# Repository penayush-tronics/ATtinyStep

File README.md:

# ATtinyStep

ATtinyStep is a compact, rechargeable, and portable offline step counter as well as speedometer. It helps in reaching your step goals at a healthy pace, while enjoying the outside world instead of doomscrolling with your neck down. It uses a 6-axis Accelrometer+Gyro IMU (Interital Measurment Unit) and the processing capabilities of the ATtiny1624 to easily count your steps automatically. As a bonus, it doubles as breakout board for the ATtiny1624, so it can be used for more projects other than a speedometer.

## How to use the ATtinyStep
Here is a labelled diagram:

#### As step counter
Connect a single cell 3.7V li-ion battery to the battery header (with correct polarity; labelled on the back). It has an built-in voltage. After that, connect the I2C OLED screen. To use it as a step counter, flip the switch to turn it on. 
On the top left corner is a Mode select button, which allows the selection between speed display and step counting modes.
On the top right corner there is a Reset button to reset the Attiny chip in case of some error/restart. Below this button is the UART programming header, labelled for convenience. 
The device will automatically start counting steps and calculating the speed of your walking or any motion. 

#### As development board
You can also use it as a breakout board for the ATtiny1624 with built in 6-axis Gyro+Accelerometer and easy to use I2C header.
When powering it as a development board, make sure to use only **3V3 power (3.3V)**, on the VCC pin either on the breakout pins, the programming header, or the I2C header. Make sure to connect GND-Ground too. **Be careful with polarity**.
Pins 8 and 9 are always pulled high due to the I2C, so use them primarily for I2C. 
Pin 13 is connected to the onboard Mode Select button, using active low. This pin can be reconfigured.
Use the reset button to restart the Attiny1624.

#### Programming
ATtinyStep uses UPDI programming for the ATtiny1624, via UART. Make sure to use 3V3 only.
An appropriate resistor is already placed in series with Tx, so an external series resistor is not required, only a UART to USB converter is needed for programming. 
Connect the GND VCC pins, and connect **UART-USB Rx to ATtinyStep Tx, and Tx to Rx, like cris-cross**.
After that it can be programmed using ArduinoIDE with the **MegaTinyCore board library**.   

### Labels

The board is thoroughly labelled with all components and pins labelled.
Here you can see the breakout pin labels, header labels, battery label **-- PLEASE DONT PUT REVERSE POLARITY--** , and accelerometer direction label.
Use these as a guide for usage. 

## How does it work
The ATinyStep works by letting the ATtiny1624 continuously gather angular orientation and acceleration data. By comparing these continuous values to known patterns, such as walking with it in your hand or pocket, it can accuratley detect a step. These actions create very specific accelration and rotation patterns, hence they can be used as reference. For example, walking with it in your hand will result in a big arc-like path, with maximum acceleration at the edges of the arc, and least in the center. This also is how your mobile device, like a phone, counts steps. The sensor being used here is from the LSM6DS series by STMicroelectronics, where the 6 stands for 6-axis. Six-axis means three-axis accelrometer and three-axis gyroscope. 

## Schematics 

KiCAD schematics can be found [here](PCB_Files/ATtinyStep.kicad_sch)

## PCB design

#### Front side:

#### Back side:

KiCAD PCB design can be found [here](PCB_Files/ATtinyStep.kicad_pcb).
Gerber files for fabrication are [here](PCB_Files/ATtinyStep-Gerbers.zip).
Position file for pick and place is [here](PCB_Files/ATtinyStep-all.pos).

## Why ATtinyStep exists
One day I was walking around my community and talking to my friend online. We were talking about walking as an exercise, and how walking faster is important. Hence, they said that they were sure I wasn't walking fast enough. I told them I walk at 6km/h, but they did not believe me. That day I had two realisations: I should take a break from my phone during walks, and I need a speedometer for myself. So, this idea was born. An offline hardware speedometer. So I can make sure I am walking at a healthy speed.
The name comes from when I was thinking about a title, and realised ATtiny sounds like 'A tiny', and well it's a step counter. So ATtinyStep came. It is pronounced 'Ay Tee tiny step' or just 'A tiny step'.

The extra breakout board pins were because it felt like a waste to have so many pins unused. So the breakout enables them to be used. 

## Demo
Coming soon :)

## Bill Of Materials (BOM)

| Sr No. | Component Description | Min Order Qty | Qty for board | Unit Price (INR) | Unit Price (USD) | Ext. Price (INR) | Ext. Price (USD) | Reference Link |
|---|---|---|---|---|---|---|---|---|
| 1 | ATTINY1624-SSU-MICROCHIP-8 Bit MCU | 1 | 1 | 226.00 | 2.38 | 226.00 | 2.38 | [Robu](https://robu.in/product/attiny1624-ssu-microchip-8-bit-mcu-avr-family-attiny1624-series-microcontrollers-avr-20-mhz-16-kb-14-pins-wsoic/) |
| 2 | LSM6DSOETR3-Stmicroelectronics | 1 | 1 | 292.00 | 3.07 | 292.00 | 3.07 | [Robu](https://robu.in/product/lsm6dsoetr3-stmicroelectronics-lsm6dsoetr3-mems-modules/) |
| 3 | 0.96 inch Yellow-Blue OLED Display Module | 1 | 1 | 179.00 | 1.88 | 179.00 | 1.88 | [Robu](https://robu.in/product/0-96-inch-yellow-yellow-blue-oled-lcd-led-display-module/) |
| 4 | AP2112K/AP2125K -3.3TRG1-Diodes Incorporated | 1 | 1 | 13.00 | 0.14 | 13.00 | 0.14 | [Robu](https://robu.in/product/ap2125k-3-3trg1-diodes-incorporated-300ma-65db-fixed-3-3v-positive-9v-sot-23-5-voltage-regulators-linear-low-drop-out-ldo-regulators-rohs/) |
| 5 | 3.7V 1500mAH Li-Po Rechargeable Battery (523450) | 1 | 1 | 232.00 | 2.44 | 232.00 | 2.44 | [Quartz Components](https://quartzcomponents.com/products/3-7v-1500mah-li-po-rechargeable-battery-523450?variant=44853316813034) |
| 6 | Toggle Slide Switch | 1 | 1 | 5.00 | 0.05 | 5.00 | 0.05 | [Quartz Components](https://quartzcomponents.com/products/toggle-slide-switch?variant=31898088833159) |
| 7 | Green LED - SMD (1206 Package) - Pack of 50 | 50 | 1 | 0.72 | 0.01 | 36.00 | 0.38 | [Quartz Components](https://quartzcomponents.com/collections/all/products/green-led-smd-1206-package-pack-of-50) |
| 8 | 1K Ohm 1206 Package 1/4W SMD Resistor 5% Tolerance (Pack of 20 Pieces) | 20 | 1 | 0.50 | 0.01 | 10.00 | 0.11 | [Quartz Components](https://quartzcomponents.com/products/1k-ohm-1206-package-1-4w-smd-resistor-5-tolerance-pack-of-20-pieces?variant=44679699792106) |
| 9 | 4.7K Ohm 1206 Package 1/4W SMD Resistor 5% Tolerance (Pack of 20 Pieces) | 20 | 3 | 0.60 | 0.01 | 12.00 | 0.13 | [Quartz Components](https://quartzcomponents.com/products/4-7k-ohm-1206-package-1-4w-smd-resistor-5-tolerance-pack-of-20-pieces?variant=44679719878890) |
| 10 | TSB005A2518B-BZCN-3.6mm 2.5mm 50mA 8mm 30,000 Times 180gf 12V SMD Tactile Switches | 4 | 2 | 2.85 | 0.03 | 11.40 | 0.12 | [Robu](https://robu.in/product/tsb005a2518b-bzcn-3-6mm-2-5mm-50ma-8mm-30000-times-180gf-12v-smd-tactile-switches-rohs/) |
| 11 | A7 / 1N4007 SMD Diode (Pack of 10) | 10 | 1 | 1.10 | 0.01 | 11.00 | 0.12 | [Quartz Components](https://quartzcomponents.com/products/m7-1n4007-smd-diode-pack-of-11?variant=43690452713706) |
| 12 | 100nF / 0.1uF (104) 50V 1206 SMD Capacitor (Pack of 10 Pieces) | 10 | 2 | 1.60 | 0.02 | 16.00 | 0.17 | [Quartz Components](https://quartzcomponents.com/products/100nf-0-1uf-104-50v-1206-smd-capacitor-pack-of-10-pieces?variant=43526822232298) |
| 13 | 16V 10uF X5R 1206 Multilayer Ceramic Capacitors MLCC | 3 | 2 | 4.57 | 0.05 | 13.71 | 0.14 | [Robu](https://robu.in/product/cl31a106kohnnwe-samsang-16v-10uf-x5r-1206-multilayer-ceramic-capacitors-mlcc-smd-smt-rohs/) |
| 14 | MLCC SMD Capacitor - 100UF, 10V, 1210 | 1 | 1 | 46.00 | 0.48 | 46.00 | 0.48 | [Robu](https://robu.in/product/lmk325abj107mm-p-taiyo-yuden-cap-smd-mlcc-100uf-10v-1210-pack-of-1/) |
| 15 | TP4056 - Battery Charging | 1 | 1 | 14.00 | 0.15 | 14.00 | 0.15 | [Quartz Components](https://quartzcomponents.com/products/tp4056-battery-charging-micro-usb) |
| 16 | Male/Female headers | 1 | 1 | 9.00 | 0.09 | 9.00 | 0.09 | [Robu](https://robu.in/product/2-54mm-1x40-pin-male-single-row-straight-short-header-strip-pack-of-3/) |
| 17 | Custom PCB | 5 | 1 | 188.80 | 1.99 | 944.00 | 9.94 | [Lion Circuits](https://www.lioncircuits.com/quote?layers=2&units=5&dimensionX=50&dimensionY=20) |
|  | **Totals:** |  | **22** | **** | **** | **2070.11** | **21.79** |  |

Price per board: ~1230 INR or ~ $12.9 USD

The spreadsheet BOM is [here](BOM.csv)

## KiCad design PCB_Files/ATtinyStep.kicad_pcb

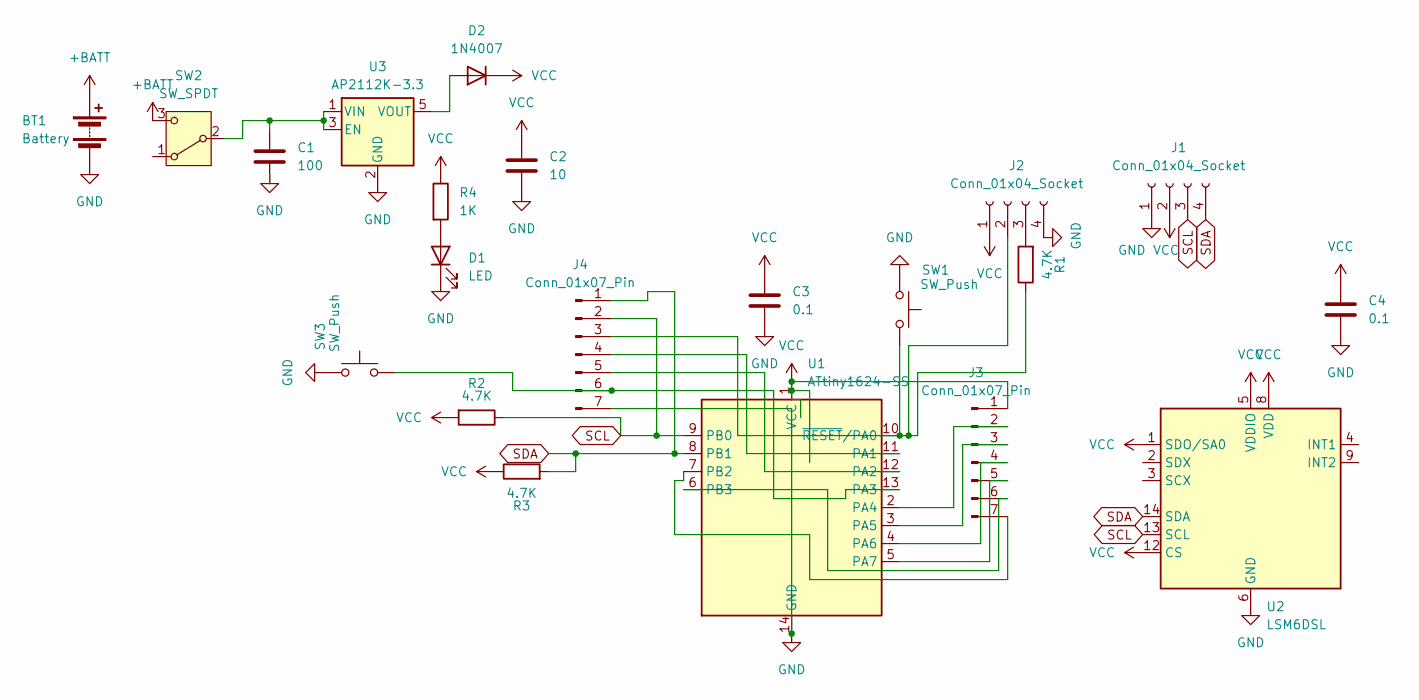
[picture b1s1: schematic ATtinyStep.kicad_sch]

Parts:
BT1: Battery; PinHeader_2x01_P2.54mm_Vertical
C1: 100; C_1210_3225Metric_Pad1.33x2.70mm_HandSolder
C2: 10; C_1206_3216Metric_Pad1.33x1.80mm_HandSolder
C3, C4: 0.1; C_1206_3216Metric_Pad1.33x1.80mm_HandSolder
D1: LED; LED_1206_3216Metric
D2: 1N4007; D_SOD-123F
J1, J2: Conn_01x04_Socket; PinHeader_1x04_P2.54mm_Vertical
J3, J4: Conn_01x07_Pin; PinHeader_1x07_P2.54mm_Vertical
R1, R2, R3: 4.7K; R_1206_3216Metric_Pad1.30x1.75mm_HandSolder
R4: 1K; R_1206_3216Metric_Pad1.30x1.75mm_HandSolder
SW1, SW3: SW_Push; SW_SPST_CK_RS282G05A3
SW2: SW_SPDT; SW_Slide_SPDT_Straight_CK_OS102011MS2Q
U1: ATtiny1624-SS; SOIC-14_3.9x8.7mm_P1.27mm
U2: LSM6DSL; LGA-14_3x2.5mm_P0.5mm_LayoutBorder3x4y
U3: AP2112K-3.3; SOT-23-5

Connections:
+BATT: BT1.1 (+), SW2.3 (C); also elsewhere on the board
GND: BT1.2 (-), C1.2, C2.2, C3.2, C4.2, D1.1 (K), J1.1, J2.4, J4.7, SW1.1, SW3.1, U1.14 (GND), U2.6 (GND), U2.7 (GND), U3.2 (GND); also elsewhere on the board
unnamed: D1.2 (A), R4.2
unnamed: D2.2 (A), U3.5 (VOUT)
unnamed: J2.2, J4.3, R1.1, SW1.2, U1.10 (~RESET/PA0)
unnamed: J2.3, R1.2
unnamed: J3.2, U1.2 (PA4)
unnamed: J3.3, U1.3 (PA5)
unnamed: J3.4, U1.4 (PA6)
unnamed: J3.5, U1.5 (PA7)
unnamed: J3.6, U1.6 (PB3)
unnamed: J3.7, U1.7 (PB2)
unnamed: J4.4, U1.11 (PA1)
unnamed: J4.5, U1.12 (PA2)
unnamed 14: J4.6, SW3.2, U1.13 (PA3); also elsewhere on the board
unnamed 15: C1.1, SW2.2 (B), U3.1 (VIN), U3.3 (EN); also elsewhere on the board
SCL: J1.3, J4.2, R2.1, U1.9 (PB0), U2.13 (SCL)
SDA: J1.4, J4.1, R3.2, U1.8 (PB1), U2.14 (SDA)
VCC: C2.1, C3.1, C4.1, D2.1 (K), J1.2, J2.1, J3.1, R2.2, R3.1, R4.1, U1.1 (VCC), U2.1 (SDO/SA0), U2.5 (VDDIO), U2.8 (VDD), U2.12 (CS)

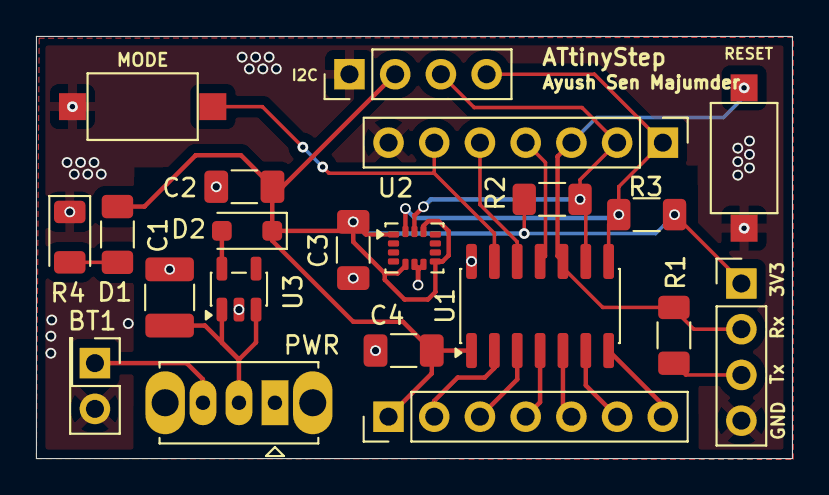
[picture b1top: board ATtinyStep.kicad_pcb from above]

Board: 2 copper layers, 42.0 x 23.5 mm, 21 parts (0 on the bottom side), 19 nets.

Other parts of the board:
MODE: SW_Push; SW_SPST_CK_RS282G05A3
PWR: SW_SPDT; SW_Slide_SPDT_Straight_CK_OS102011MS2Q

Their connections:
+BATT: PWR.3 (C); also elsewhere on the board
GND: MODE.1; also elsewhere on the board
unnamed 14: MODE.2; also elsewhere on the board
unnamed 15: PWR.2 (B); also elsewhere on the board
